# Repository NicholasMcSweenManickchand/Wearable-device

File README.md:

The goal of this project is to create a custom wearable that can gather data and interpret from that data the hear rate, step count, etc. 
I want it to do this locally on the micro controller (edge computing). This project will broadcast this data (via Bluetooth) into an app or
a UX of some kind to make the data easily readable for users.

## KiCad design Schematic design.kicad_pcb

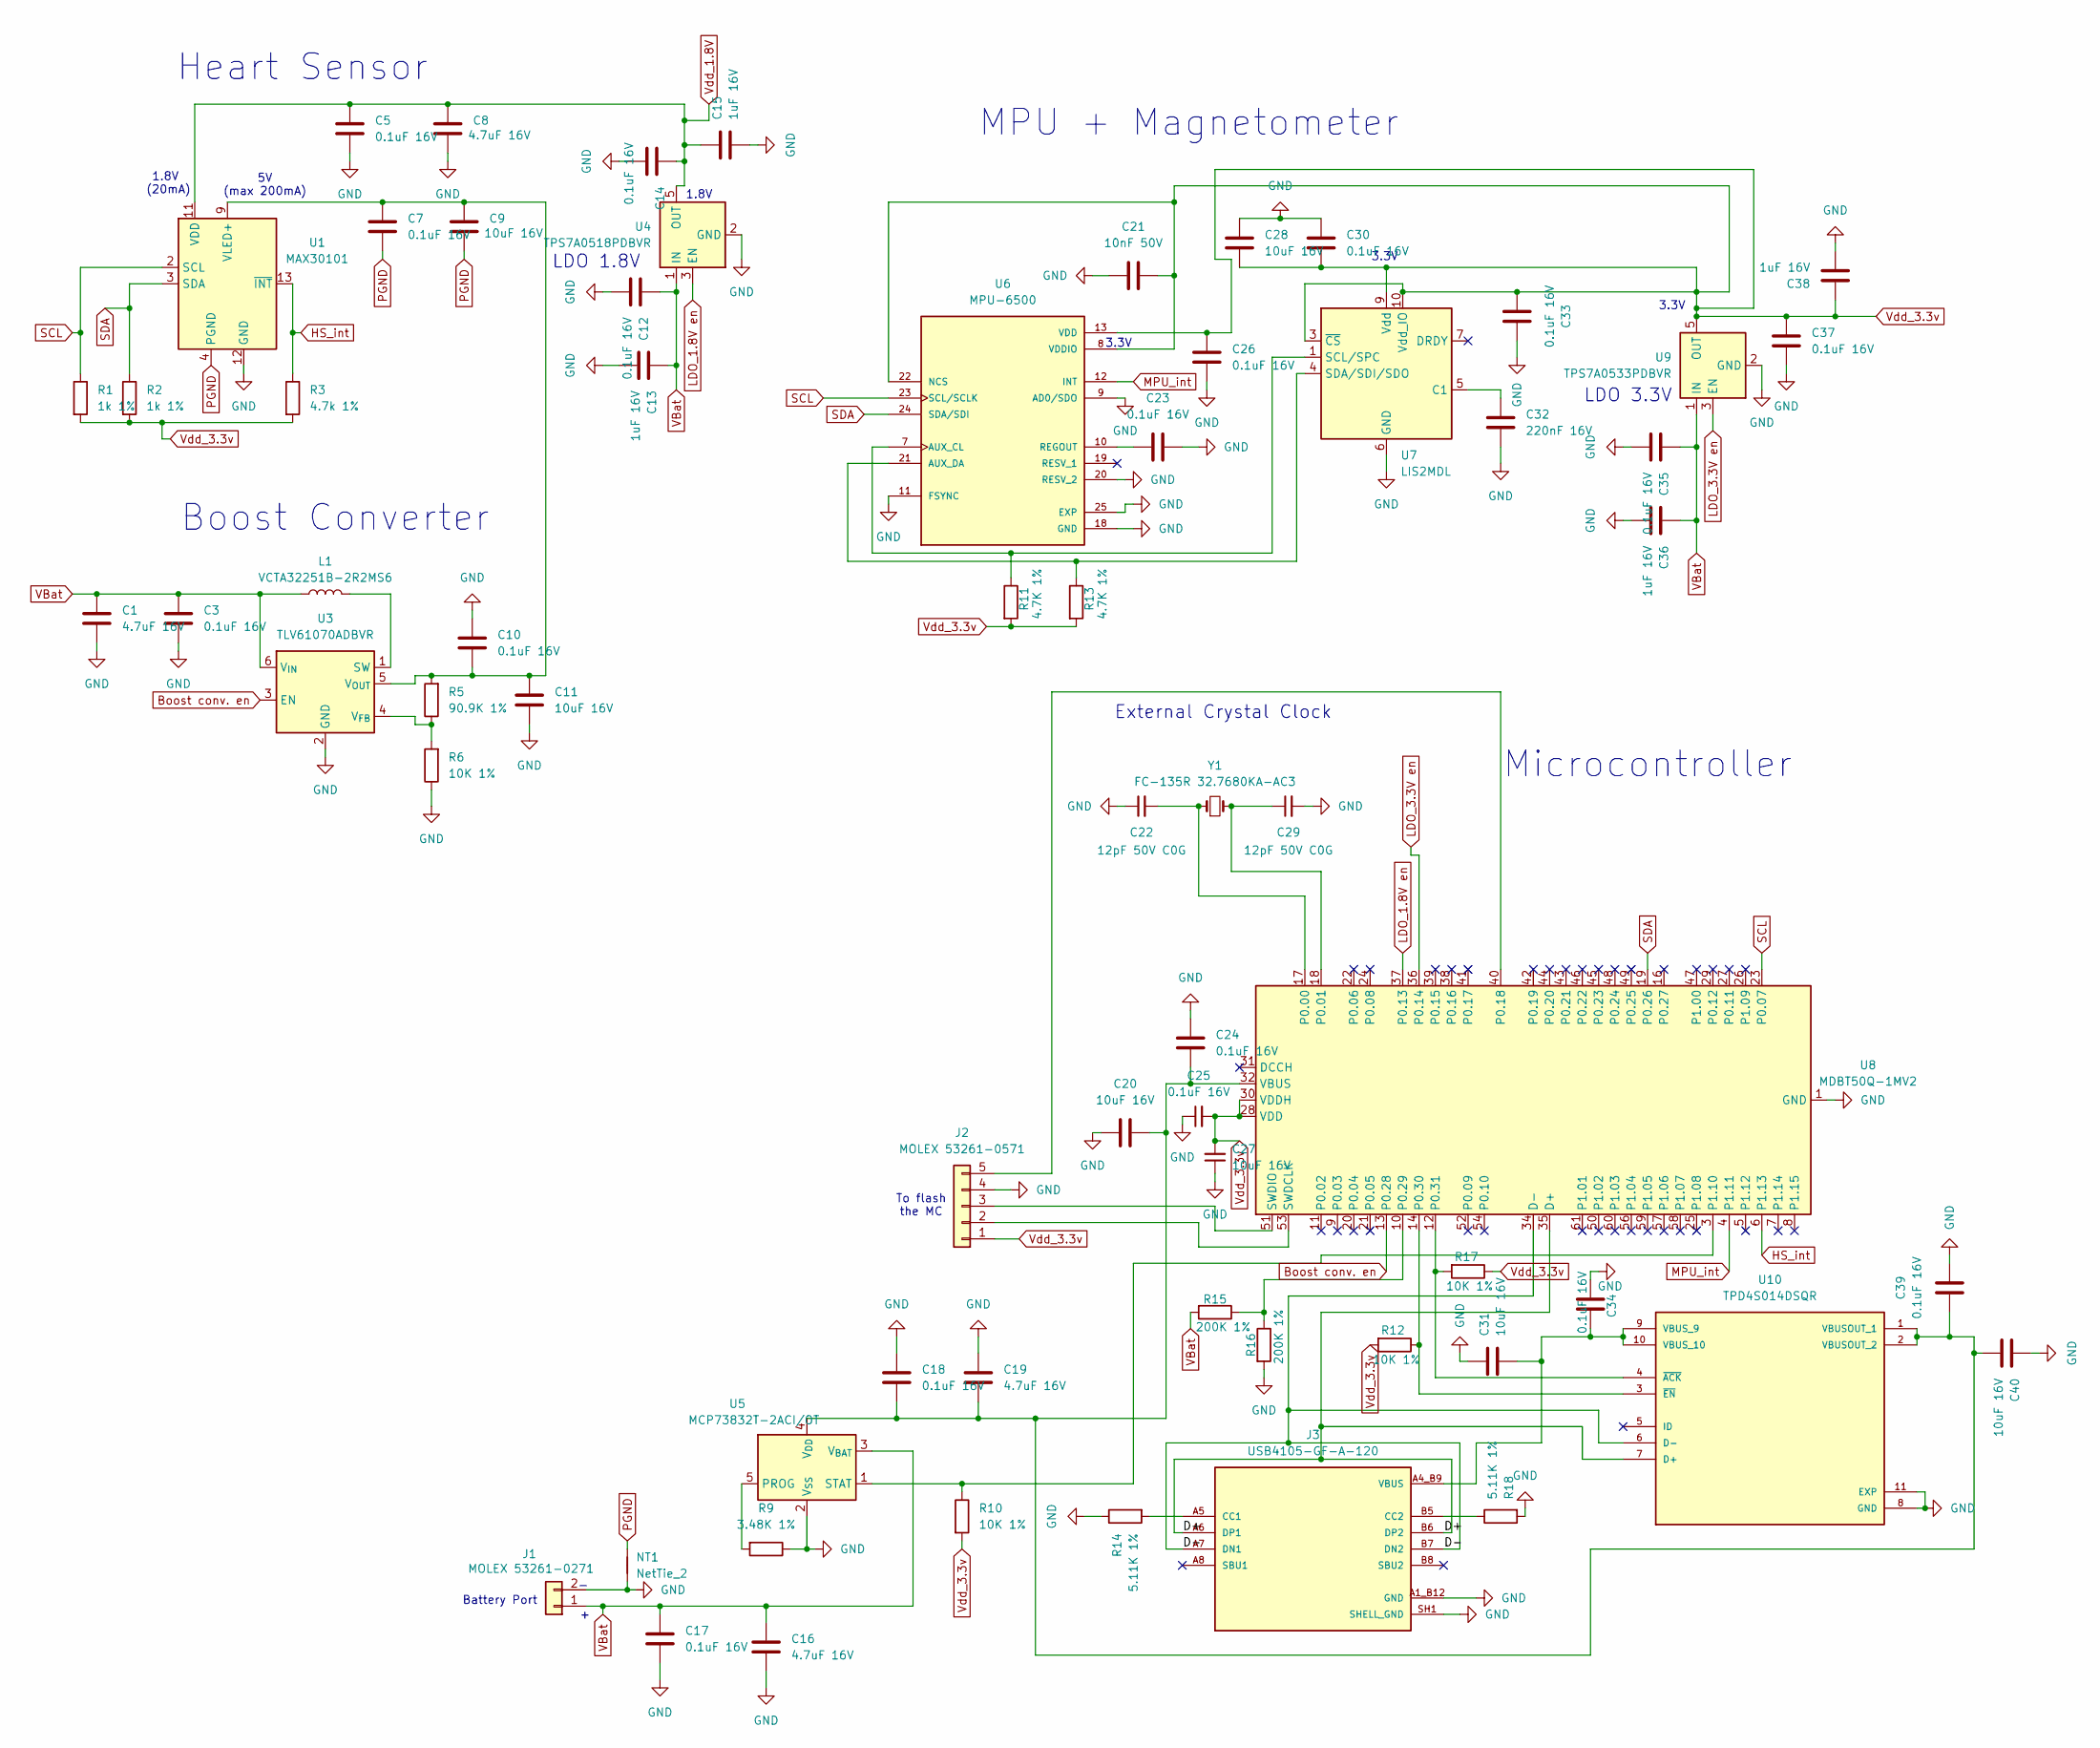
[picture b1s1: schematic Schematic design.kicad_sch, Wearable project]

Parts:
C1, C8, C16, C19: 4.7uF 16V; C_0603_1608Metric; MPN CL10A475KO8NQNC
C3, C5, C7, C10, C12, C14, C17, C18, C23, C24, C25, C26, C30, C33, C34, C35, C37, C39: 0.1uF 16V; C_0402_1005Metric; MPN CL05A104KO5NNNC
C9, C11, C20, C27, C28, C31, C40: 10uF 16V; C_0603_1608Metric; MPN CL10A106MO8NRNC
C13, C15, C36, C38: 1uF 16V; C_0603_1608Metric; MPN CL10A105KO8NNNC
C21: 10nF 50V; C_0402_1005Metric; MPN CL05B103KB5NNNC
C22, C29: 12pF 50V C0G; C_0402_1005Metric; MPN CL05C120JB5NNNC
C32: 220nF 16V; C_0402_1005Metric; MPN CL05B224KO5NNNC
J1: MOLEX 53261-0271; Molex_PicoBlade_53261-0271_1x02-1MP_P1.25mm_Horizontal; MPN 53261-0271
J2: MOLEX 53261-0571; Molex_PicoBlade_53261-0571_1x05-1MP_P1.25mm_Horizontal; MPN 53261-0571
J3: USB4105-GF-A-120; GCT_USB4105-GF-A-120; PARTREV B3
L1: VCTA32251B-2R2MS6; L_1210_3225Metric; MPN VCTA32251B-2R2MS6
NT1: NetTie_2
R1, R2: 1k 1%; R_0402_1005Metric; MPN RC0402FR-071KL
R3: 4.7k 1%; R_0402_1005Metric; MPN RC0402FR-074K7L
R5: 90.9K 1%; R_0402_1005Metric; MPN RC0402FR-0790K9L
R6, R10, R12, R17: 10K 1%; R_0402_1005Metric; MPN RC0402FR-0710KL
R9: 3.48K 1%; R_0402_1005Metric; MPN RC0402FR-073K48L
R11, R13: 4.7K 1%; R_0402_1005Metric; MPN RC0402FR-074K7L
R14, R18: 5.11K 1%; R_0402_1005Metric; MPN RC0402FR-075K11L
R15, R16: 200K 1%; R_0402_1005Metric; MPN RC0402FR-07200KL
U1: MAX30101; Maxim_OLGA-14_3.3x5.6mm_P0.8mm; MPN MAX30101EFD+T
U3: TLV61070ADBVR; SOT-23-6; MPN TLV61070ADBVR
U4: TPS7A0518PDBVR; SOT-23-5; MPN TPS7A0518PDBVR
U5: MCP73832T-2ACI/OT; SOT-23-5; MPN MCP73832T-2ACI/OT
U6: MPU-6500; QFN40P300X300X95-25N; PARTREV 1.3
U7: LIS2MDL; LGA-12_2x2mm_P0.5mm; MPN LIS2MDLTR
U8: MDBT50Q-1MV2; Raytac_MDBT50Q; MPN MDBT50Q-1MV2
U9: TPS7A0533PDBVR; SOT-23-5; MPN TPS7A0533PDBVR
U10: TPD4S014DSQR; SON40P200X200X80-11N; PARTREV E
Y1: FC-135R 32.7680KA-AC3; Crystal_SMD_3215-2Pin_3.2x1.5mm; MPN FC-135R 32.7680KA-AC3

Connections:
/D+: J3.A6 (DP1), J3.B6 (DP2), U8.35 (D+), U10.7 (D+)
/D-: J3.A7 (DN1), J3.B7 (DN2), U8.34 (D-), U10.6 (D-)
Boost conv. en: U3.3 (EN), U8.13 (P0.28)
GND: C1.2, C3.2, C5.2, C8.2, C10.1, C11.2, C12.2, C13.2, C14.2, C15.2, C16.2, C17.2, C18.1, C19.1, C20.1, C21.2, C22.1, C23.2, C24.1, C25.1, C26.1, C27.1, C28.2, C29.2, C30.2, C31.2, C32.1, C33.2, C34.1, C35.2, C36.2, C37.2, C38.2, C39.2, C40.2, J1.2, J2.4, J3.A1_B12 (GND), J3.B1_A12 (GND), J3.SH1 (SHELL_GND), J3.SH2 (SHELL_GND), J3.SH3 (SHELL_GND), J3.SH4 (SHELL_GND), NT1.1, R6.1, R9.1, R14.1, R16.2, R18.2, U1.12 (GND), U3.2 (GND), U4.2 (GND), U5.2 (V_{SS}), U6.9 (AD0/SDO), U6.11 (FSYNC), U6.18 (GND), U6.20 (RESV_2), U6.25 (EXP), U7.6 (GND), U7.8 (GND), U8.1 (GND), U8.2 (GND), U8.15 (GND), U8.33 (GND), U8.55 (GND), U9.2 (GND), U10.8 (GND), U10.11 (EXP)
HS_int: R3.1, U1.13 (~INT), U8.6 (P1.13)
LDO_1.8V en: U4.3 (EN), U8.37 (P0.13)
LDO_3.3V en: U8.36 (P0.14), U9.3 (EN)
MPU_int: U6.12 (INT), U8.4 (P1.11)
unnamed: J2.2, U8.53 (SWDCLK)
unnamed: J2.3, U8.51 (SWDIO)
unnamed: J2.5, U8.40 (P0.18)
unnamed: J3.A5 (CC1), R14.2
unnamed: J3.B5 (CC2), R18.1
unnamed: L1.2, U3.1 (SW)
unnamed: R5.1, R6.2, U3.4 (V_{FB})
unnamed: C7.1, C9.1, C10.2, C11.1, R5.2, U1.9 (VLED+), U1.10 (VLED+), U3.5 (V_{OUT})
unnamed: R9.2, U5.5 (PROG)
unnamed: R10.1, U5.1 (STAT), U8.3 (P1.10)
unnamed: R11.1, U6.7 (AUX_CL), U7.1 (SCL/SPC)
unnamed: R13.1, U6.21 (AUX_DA), U7.4 (SDA/SDI/SDO)
unnamed: C23.1, U6.10 (REGOUT)
unnamed: C32.2, U7.5 (C1)
unnamed: C22.2, U8.17 (P0.00), Y1.1
unnamed: C29.1, U8.18 (P0.01), Y1.2
unnamed: R15.1, R16.1, U8.10 (P0.29)
unnamed: C18.2, C19.2, C20.2, C24.2, C39.1, C40.1, U5.4 (V_{DD}), U8.32 (VBUS), U10.1 (VBUSOUT_1), U10.2 (VBUSOUT_2)
unnamed: R17.2, U8.12 (P0.31), U10.4 (~ACK)
unnamed: R12.1, U8.14 (P0.30), U10.3 (~EN)
PGND: C7.2, C9.2, NT1.2, U1.4 (PGND)
SCL: R1.1, U1.2 (SCL), U6.23 (SCL/SCLK), U8.23 (P0.07)
SDA: R2.1, U1.3 (SDA), U6.24 (SDA/SDI), U8.19 (P0.26)
VBUS: C31.1, C34.2, J3.A4_B9 (VBUS), J3.B4_A9 (VBUS), U10.9 (VBUS_9), U10.10 (VBUS_10)
VBat: C1.1, C3.1, C12.1, C13.1, C16.1, C17.1, C35.1, C36.1, J1.1, L1.1, R15.2, U3.6 (V_{IN}), U4.1 (IN), U5.3 (V_{BAT}), U9.1 (IN)
Vdd_1.8V: C5.1, C8.1, C14.1, C15.1, U1.11 (VDD), U4.5 (OUT)
Vdd_3.3v: C21.1, C25.2, C26.2, C27.2, C28.1, C30.1, C33.1, C37.1, C38.1, J2.1, R1.2, R2.2, R3.2, R10.2, R11.2, R12.2, R13.2, R17.1, U6.8 (VDDIO), U6.13 (VDD), U6.22 (NCS), U7.3 (~CS), U7.9 (Vdd), U7.10 (Vdd_IO), U8.28 (VDD), U8.30 (VDDH), U9.5 (OUT)

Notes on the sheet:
To flash the MC
1.8V (20mA)
Battery Port
LDO 3.3V
5V (max 200mA)
3.3V
LDO 1.8V
1.8V
Microcontroller
Heart Sensor
Boost Converter
External Crystal Clock
MPU + Magnetometer
3.3V

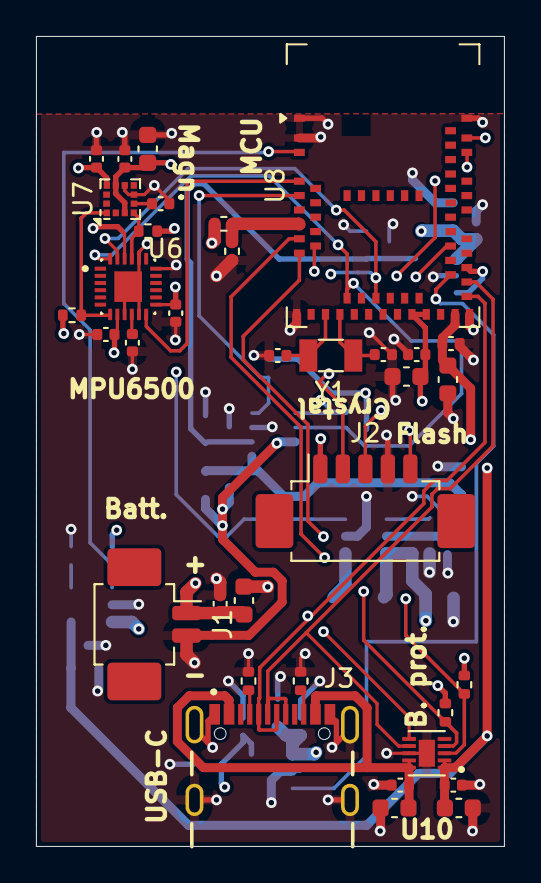
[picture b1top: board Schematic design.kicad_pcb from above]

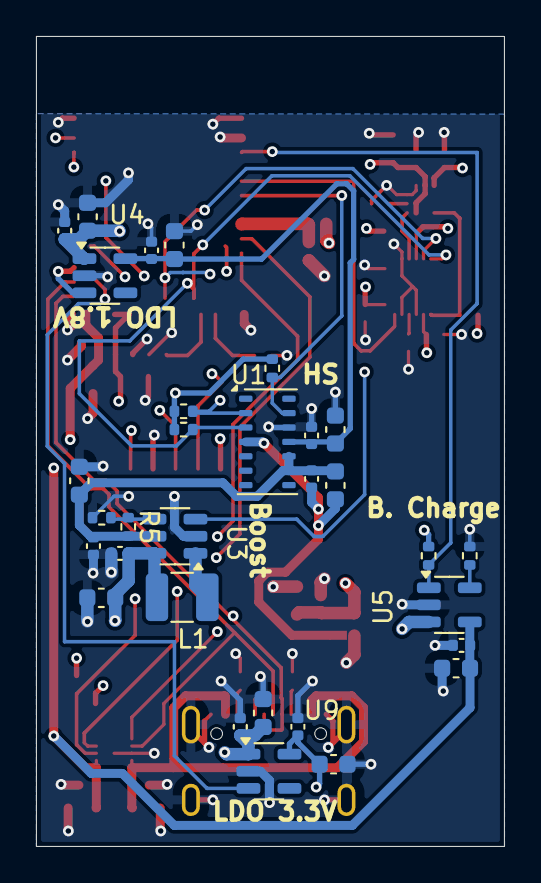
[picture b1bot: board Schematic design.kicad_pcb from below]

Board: 4 copper layers, 26.0 x 45.0 mm, 67 parts (31 on the bottom side), 35 nets.
